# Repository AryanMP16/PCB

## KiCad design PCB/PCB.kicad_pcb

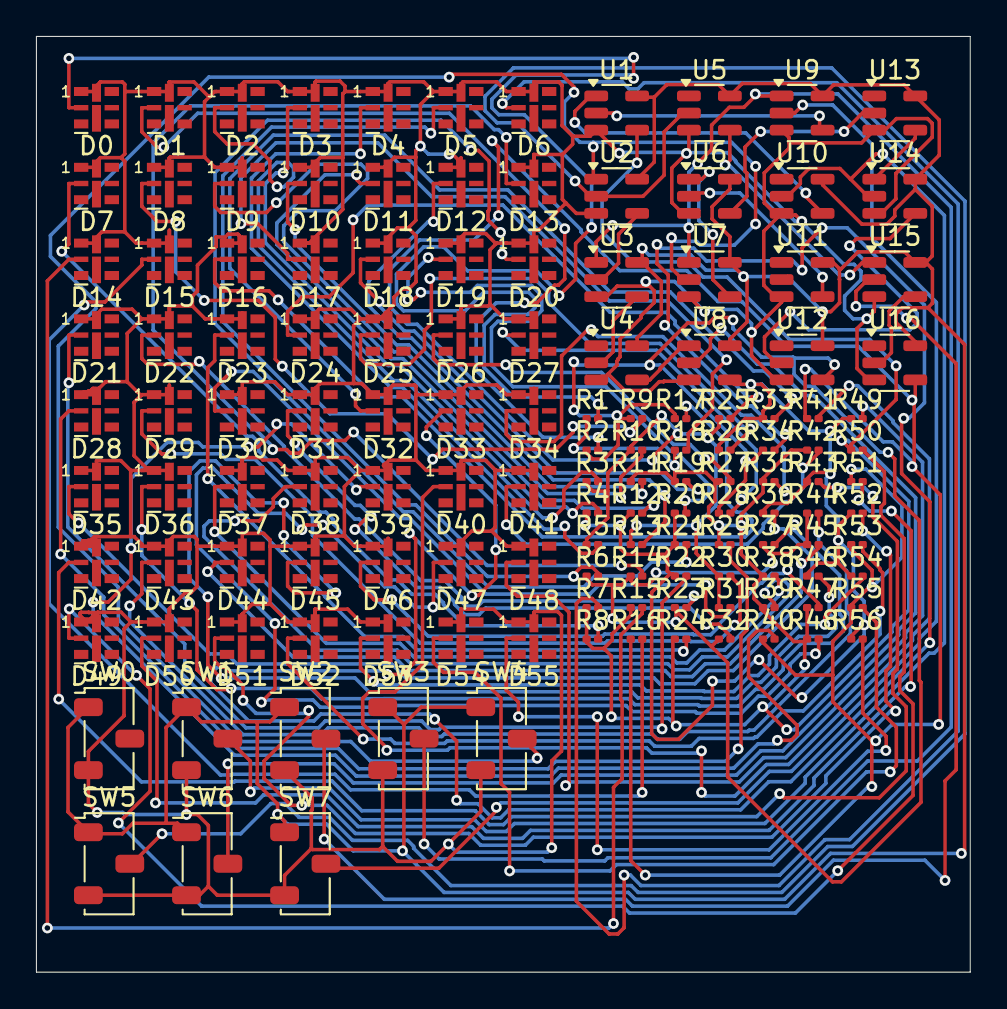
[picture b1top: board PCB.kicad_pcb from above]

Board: 2 copper layers, 51.9 x 52.0 mm, 136 parts (0 on the bottom side), 82 nets.

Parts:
D0, D1, D2, D3, D4, D5, D6, D7, D8, D9, D10, D11, D12, D13, D14, D15, D16, D17, D18, D19, D20, D21, D22, D23, D24, D25, D26, D27, D28, D29, D30, D31, D32, D33, D34, D35, D36, D37, D38, D39, D40, D41, D42, D43, D44, D45, D46, D47, D48, D49, D50, D51, D52, D53, D54, D55: LED; LED-APA102-2020
R1, R2, R3, R4, R5, R6, R7, R8, R9, R10, R11, R12, R13, R14, R15, R16, R17, R18, R19, R20, R21, R22, R23, R24, R25, R26, R27, R28, R29, R30, R31, R32, R33, R34, R35, R36, R37, R38, R39, R40, R41, R42, R43, R44, R45, R46, R47, R48, R49, R50, R51, R52, R53, R54, R55, R56: R_0201_0603Metric
SW0, SW1, SW2, SW3, SW4, SW5, SW6, SW7: SW_Nidec_CAS-120A1; Nidec_Copal_CAS-120A
U1, U9: SN74LVC1G00DBV; SOT-23-5
U2, U3, U6, U7, U8, U14, U15: 74AHC1G00; SOT-23-5
U4, U5, U10, U11, U12, U13, U16: SN74LVC1G14DBV; SOT-23-5

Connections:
GND: D0.1 (K), D1.1 (K), D2.1 (K), D3.1 (K), D4.1 (K), D5.1 (K), D6.1 (K), D7.1 (K), D8.1 (K), D9.1 (K), D10.1 (K), D11.1 (K), D12.1 (K), D13.1 (K), D14.1 (K), D15.1 (K), D16.1 (K), D17.1 (K), D18.1 (K), D19.1 (K), D20.1 (K), D21.1 (K), D22.1 (K), D23.1 (K), D24.1 (K), D25.1 (K), D26.1 (K), D27.1 (K), D28.1 (K), D29.1 (K), D30.1 (K), D31.1 (K), D32.1 (K), D33.1 (K), D34.1 (K), D35.1 (K), D36.1 (K), D37.1 (K), D38.1 (K), D39.1 (K), D40.1 (K), D41.1 (K), D42.1 (K), D43.1 (K), D44.1 (K), D45.1 (K), D46.1 (K), D47.1 (K), D48.1 (K), D49.1 (K), D50.1 (K), D51.1 (K), D52.1 (K), D53.1 (K), D54.1 (K), D55.1 (K), SW0.3 (A), SW1.3 (A), SW2.3 (A), SW3.3 (A), SW4.3 (A), SW5.3 (A), SW6.3 (A), SW7.3 (A), U1.3 (GND), U2.3 (GND), U3.3 (GND), U4.3 (GND), U5.3 (GND), U6.3 (GND), U7.3 (GND), U8.3 (GND), U9.3 (GND), U10.3 (GND), U11.3 (GND), U12.3 (GND), U13.3 (GND), U14.3 (GND), U15.3 (GND), U16.3 (GND)
unnamed: D0.2 (A), R1.2
unnamed: D1.2 (A), R2.2
unnamed: D2.2 (A), R3.2
unnamed: D3.2 (A), R4.2
unnamed: D4.2 (A), R5.2
unnamed: D5.2 (A), R6.2
unnamed: D6.2 (A), R7.2
unnamed: D7.2 (A), R8.2
unnamed: D8.2 (A), R9.2
unnamed: D9.2 (A), R10.2
unnamed: D10.2 (A), R11.2
unnamed: D11.2 (A), R12.2
unnamed: D12.2 (A), R13.2
unnamed: D13.2 (A), R14.2
unnamed: D14.2 (A), R15.2
unnamed: D15.2 (A), R16.2
unnamed: D16.2 (A), R17.2
unnamed: D17.2 (A), R18.2
unnamed: D18.2 (A), R19.2
unnamed: D19.2 (A), R20.2
unnamed: D20.2 (A), R21.2
unnamed: D21.2 (A), R22.2
unnamed: D22.2 (A), R23.2
unnamed: D23.2 (A), R24.2
unnamed: D24.2 (A), R25.2
unnamed: D25.2 (A), R26.2
unnamed: D26.2 (A), R27.2
unnamed: D27.2 (A), R28.2
unnamed: D28.2 (A), R29.2
unnamed: D29.2 (A), R30.2
unnamed: D30.2 (A), R31.2
unnamed: D31.2 (A), R32.2
unnamed: D32.2 (A), R33.2
unnamed: D33.2 (A), R34.2
unnamed: D34.2 (A), R35.2
unnamed: D35.2 (A), R36.2
unnamed: D36.2 (A), R37.2
unnamed: D37.2 (A), R38.2
unnamed: D38.2 (A), R39.2
unnamed: D39.2 (A), R40.2
unnamed: D40.2 (A), R41.2
unnamed: D41.2 (A), R42.2
unnamed: D42.2 (A), R43.2
unnamed: D43.2 (A), R44.2
unnamed: D44.2 (A), R45.2
unnamed: D45.2 (A), R46.2
unnamed: D46.2 (A), R47.2
unnamed: D47.2 (A), R48.2
unnamed: D48.2 (A), R49.2
unnamed: D49.2 (A), R50.2
unnamed: D50.2 (A), R51.2
unnamed: D51.2 (A), R52.2
unnamed: D52.2 (A), R53.2
unnamed: D53.2 (A), R54.2
unnamed: D54.2 (A), R55.2
unnamed: D55.2 (A), R56.2
unnamed: R1.1, R7.1, R8.1, R11.1, R15.1, R18.1, R19.1, R24.1, R27.1, R29.1, R35.1, R38.1, R39.1, R42.1, R47.1, R48.1, R50.1, U1.4
unnamed: R3.1, R5.1, R10.1, R13.1, R16.1, R25.1, R30.1, R31.1, R40.1, R41.1, R51.1, R53.1, R55.1, U16.4
unnamed: R4.1, R12.1, R20.1, R21.1, R22.1, R26.1, R33.1, R36.1, R43.1, R46.1, R49.1, R52.1, R54.1, R56.1, U8.4
unnamed: R2.1, R6.1, R9.1, R14.1, R17.1, R23.1, R28.1, R32.1, R34.1, R37.1, R44.1, R45.1, U12.4
unnamed: SW0.2 (B), U11.2
unnamed: SW1.2 (B), U10.2, U14.2
unnamed: SW2.2 (B), U15.2
unnamed: SW3.2 (B), U3.1, U7.1, U9.1
unnamed: SW4.2 (B), U2.1, U7.2
unnamed: SW5.2 (B), U2.2, U5.2
unnamed: SW6.2 (B), U8.2
unnamed: SW7.2 (B), U9.2
unnamed: U1.1, U10.4
unnamed: U1.2, U9.4
unnamed: U2.4, U3.2
unnamed: U3.4, U4.2
unnamed: U4.4, U8.1
unnamed: U6.1, U7.4
unnamed: U6.2, U11.4
unnamed: U12.2, U14.4
unnamed: U6.4, U13.2
unnamed: U13.4, U14.1
unnamed: U5.4, U15.1
unnamed: U15.4, U16.2
VCC: SW0.1 (C), SW1.1 (C), SW2.1 (C), SW3.1 (C), SW4.1 (C), SW5.1 (C), SW6.1 (C), SW7.1 (C), U1.5 (VCC), U2.5 (VCC), U3.5 (VCC), U4.5 (VCC), U5.5 (VCC), U6.5 (VCC), U7.5 (VCC), U8.5 (VCC), U9.5 (VCC), U10.5 (VCC), U11.5 (VCC), U12.5 (VCC), U13.5 (VCC), U14.5 (VCC), U15.5 (VCC), U16.5 (VCC)

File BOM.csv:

"Id";"Designator";"Footprint";"Quantity";"Designation";"Supplier and ref";
1;"D43,D10,D21,D33,D4,D40,D44,D23,D50,D53,D7,D42,D24,D6,D11,D17,D12,D37,D34,D15,D25,D49,D46,D9,D35,D26,D14,D48,D20,D3,D54,D1,D51,D19,D16,D2,D0,D28,D22,D13,D5,D38,D31,D30,D8,D36,D18,D45,D39,D47,D55,D32,D52,D41,D29,D27";"LED-APA102-2020";56;"LED";;;
2;"U1,U9";"SOT-23-5";2;"SN74LVC1G00DBV";;;
3;"R9,R35,R46,R15,R6,R17,R55,R2,R1,R45,R24,R37,R20,R16,R27,R7,R22,R28,R5,R43,R38,R44,R50,R8,R32,R11,R25,R54,R51,R3,R47,R34,R39,R14,R36,R49,R10,R30,R13,R31,R52,R41,R48,R26,R42,R40,R4,R33,R56,R29,R53,R18,R21,R19,R12,R23";"R_0201_0603Metric";56;"~";;;
4;"U7,U3,U14,U15,U8,U2,U6";"SOT-23-5";7;"74AHC1G00";;;
5;"SW0,SW7,SW4,SW2,SW1,SW3,SW6,SW5";"Nidec_Copal_CAS-120A";8;"SW_Nidec_CAS-120A1";;;
6;"U12,U5,U10,U4,U11,U16,U13";"SOT-23-5";7;"SN74LVC1G14DBV";;;

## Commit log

2025-01-05 just putting this online
2026-01-30 loki secrets dump
